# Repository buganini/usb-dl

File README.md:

# USB
    Application: ESP32-C3
    Pinouts: 2.54 2.0 1.27 1.0
    * G: Gnd
    * +: USB D+
    * -: USB D-
    * V: 3.3v or 5v output

# ESP32
    Application: ESP32
    Pinouts: 2.54 2.0
    * En
    * IO0
    * Gnd
    * RX
    * TX
    * V: 3.3v or 5v output

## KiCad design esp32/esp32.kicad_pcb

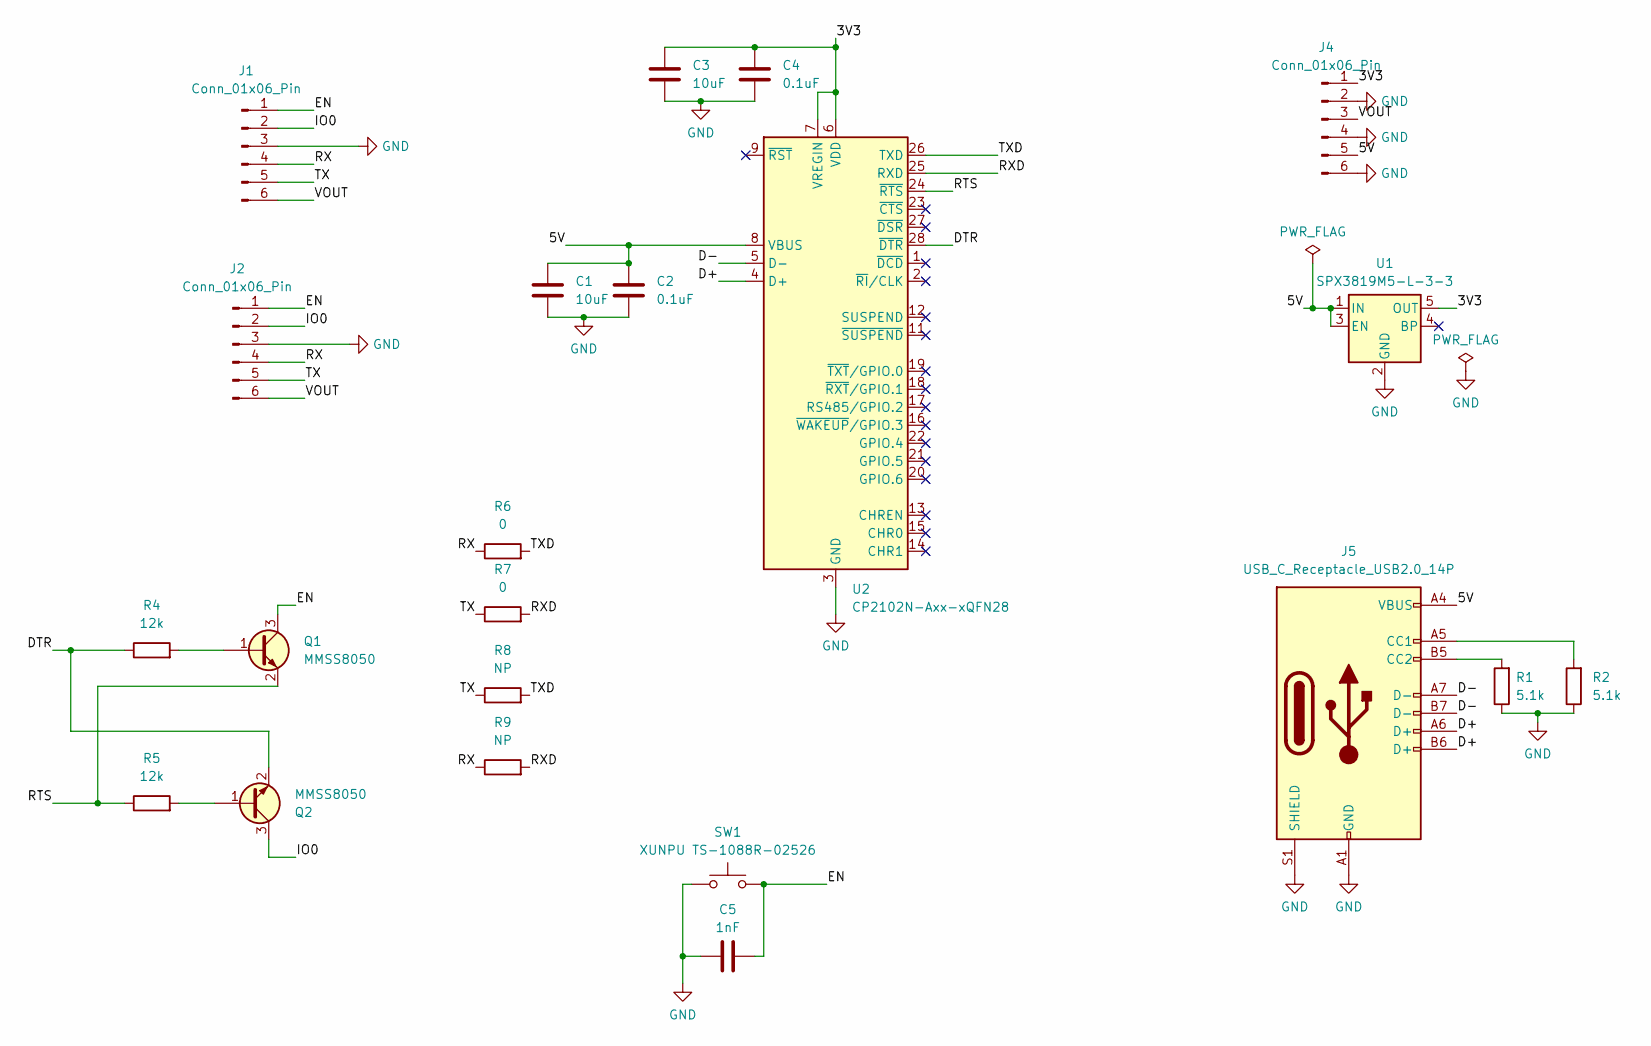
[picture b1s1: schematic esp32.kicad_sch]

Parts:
C1, C3: 10uF; C_0603_1608Metric
C2, C4: 0.1uF; C_0603_1608Metric
C5: 1nF; C_0603_1608Metric
J1: Conn_01x06_Pin; PinHeader_1x06_P2.54mm_Vertical
J2: Conn_01x06_Pin; PinHeader_1x06_P2.00mm_Vertical
J4: Conn_01x06_Pin; PinHeader_2x03_P2.54mm_Vertical
J5: USB_C_Receptacle_USB2.0_14P; USB_C_Receptacle_XKB_U262-16XN-4BVC11
Q1, Q2: MMSS8050; SOT-23
R1, R2: 5.1k; R_0603_1608Metric
R4, R5: 12k; R_0603_1608Metric
R6, R7: 0; R_0603_1608Metric
R8, R9: NP; R_0603_1608Metric
SW1: XUNPU TS-1088R-02526; SW_Push_SPST_NO_Alps_SKRK
U1: SPX3819M5-L-3-3; SOT-23-5
U2: CP2102N-Axx-xQFN28; QFN-28-1EP_5x5mm_P0.5mm_EP3.35x3.35mm

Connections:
/3V3: C3.1, C4.1, J4.1, U1.5 (OUT), U2.6 (VDD), U2.7 (VREGIN)
/5V: C1.1, C2.1, J4.5, J5.A4 (VBUS), J5.A9 (VBUS), J5.B4 (VBUS), J5.B9 (VBUS), U1.1 (IN), U1.3 (EN), U2.8 (VBUS)
/D+: J5.A6 (D+), J5.B6 (D+), U2.4 (D+)
/D-: J5.A7 (D-), J5.B7 (D-), U2.5 (D-)
/DTR: Q2.2 (E), R4.1, U2.28 (~DTR)
/EN: C5.2, J1.1, J2.1, Q1.3 (C), SW1.2
/IO0: J1.2, J2.2, Q2.3 (C)
/RTS: Q1.2 (E), R5.1, U2.24 (~RTS)
/RX: J1.4, J2.4, R6.1, R9.1
/RXD: R7.2, R9.2, U2.25 (RXD)
/TX: J1.5, J2.5, R7.1, R8.1
/TXD: R6.2, R8.2, U2.26 (TXD)
/VOUT: J1.6, J2.6, J4.3
GND: C1.2, C2.2, C3.2, C4.2, C5.1, J1.3, J2.3, J4.2, J4.4, J4.6, J5.A1 (GND), J5.A12 (GND), J5.B1 (GND), J5.B12 (GND), J5.S1 (SHIELD), R1.1, R2.1, SW1.1, U1.2 (GND), U2.3 (GND), U2.29 (GND)
unnamed: J5.A5 (CC1), R2.2
unnamed: J5.B5 (CC2), R1.2
unnamed: Q1.1 (B), R4.2
unnamed: Q2.1 (B), R5.2

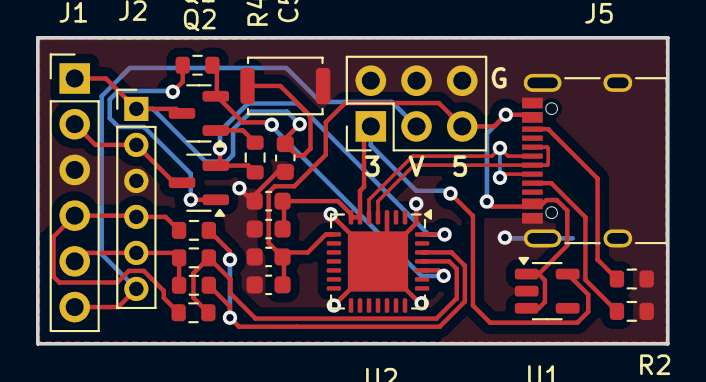
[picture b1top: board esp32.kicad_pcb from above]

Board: 2 copper layers, 35.0 x 17.0 mm, 22 parts (0 on the bottom side), 18 nets.

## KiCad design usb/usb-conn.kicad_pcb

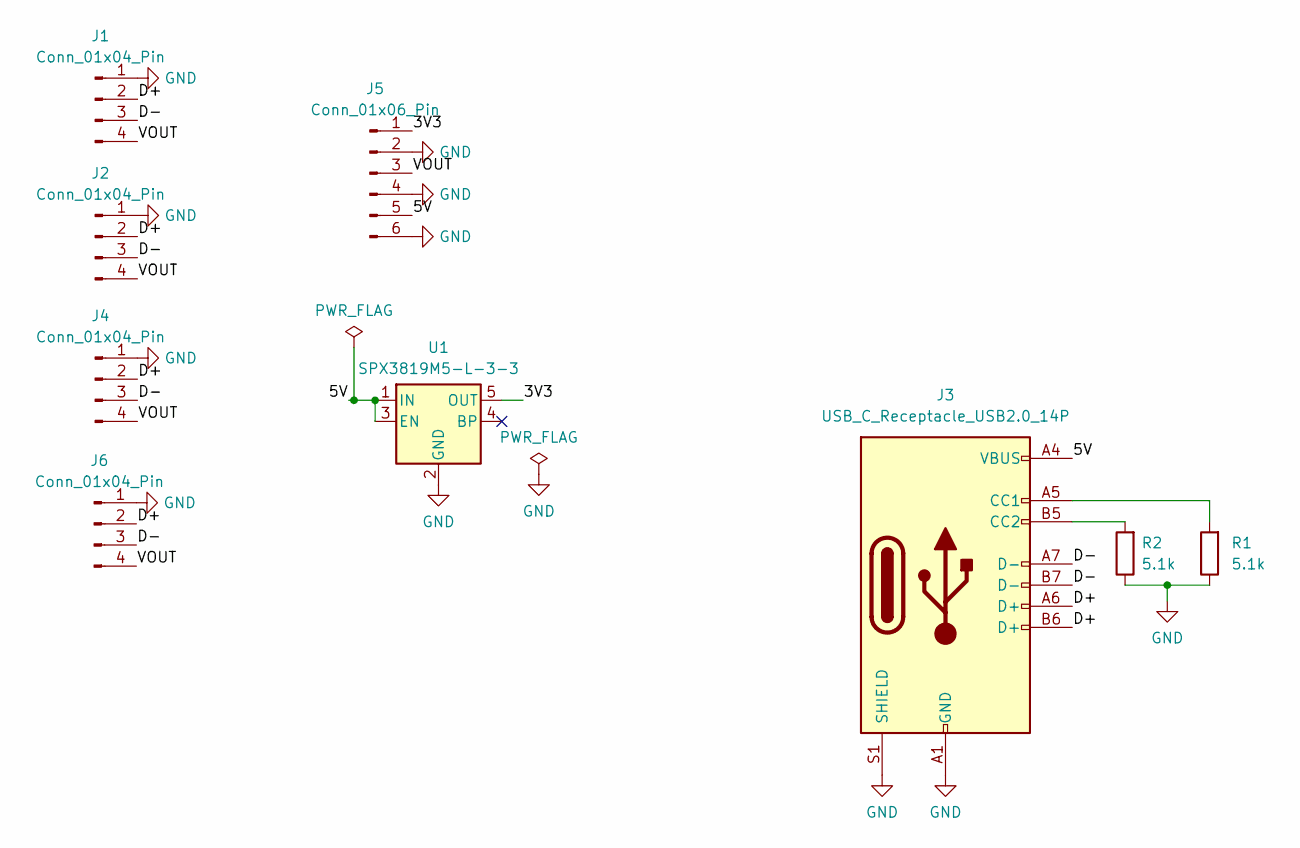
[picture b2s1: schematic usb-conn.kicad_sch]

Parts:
J1: Conn_01x04_Pin; PinHeader_1x04_P2.54mm_Vertical
J2: Conn_01x04_Pin; PinHeader_1x04_P2.00mm_Vertical
J3: USB_C_Receptacle_USB2.0_14P; USB_C_Receptacle_XKB_U262-16XN-4BVC11
J4: Conn_01x04_Pin; PinHeader_1x04_P1.27mm_Vertical
J5: Conn_01x06_Pin; PinHeader_2x03_P2.54mm_Vertical
J6: Conn_01x04_Pin; PinHeader_1x04_P1.00mm_Vertical
R1, R2: 5.1k; R_0603_1608Metric
U1: SPX3819M5-L-3-3; SOT-23-5

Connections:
/3V3: J5.1, U1.5 (OUT)
/5V: J3.A4 (VBUS), J3.A9 (VBUS), J3.B4 (VBUS), J3.B9 (VBUS), J5.5, U1.1 (IN), U1.3 (EN)
/D+: J1.2, J2.2, J3.A6 (D+), J3.B6 (D+), J4.2, J6.2
/D-: J1.3, J2.3, J3.A7 (D-), J3.B7 (D-), J4.3, J6.3
/VOUT: J1.4, J2.4, J4.4, J5.3, J6.4
GND: J1.1, J2.1, J3.A1 (GND), J3.A12 (GND), J3.B1 (GND), J3.B12 (GND), J3.S1 (SHIELD), J4.1, J5.2, J5.4, J5.6, J6.1, R1.1, R2.1, U1.2 (GND)
unnamed: J3.A5 (CC1), R1.2
unnamed: J3.B5 (CC2), R2.2

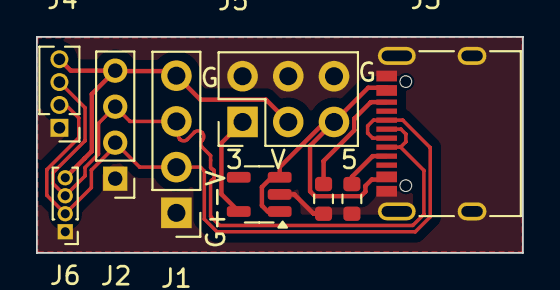
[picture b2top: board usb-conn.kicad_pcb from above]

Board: 2 copper layers, 27.0 x 12.0 mm, 9 parts (0 on the bottom side), 8 nets.

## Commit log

2024-06-04 add usb-conn
2024-06-04 usb-conn: fix connector
2024-06-05 usb-conn: update fp cache
2024-06-06 usb-conn: layout update
2024-06-18 usb-conn: minor layout update
2024-08-15 move files into usb folder
2024-08-15 add readme
2024-08-15 add esp32 board
2024-08-18 esp32: reduce board length
2024-08-18 usb: add 2.0 pinout
2024-08-18 esp32: move trace away from board edge
2024-08-18 usb-conn: move trace away from board edge
2024-08-21 readme: update pinouts
2024-08-21 update with kicad 8
2024-08-29 esp32: fix reset button
2024-10-31 esp32: remove R on TX
